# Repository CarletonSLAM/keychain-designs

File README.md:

#PCB Keychains

EAGLE CAD project files for IEEE Carleton University promotional keychains.

(c) Hasith Vidanamadura, 2015

###Todo

- [x] Finish initial layout
- [ ] FInish picking component values for timing control and LEDs.

###License

This is a MIT-licensed project.

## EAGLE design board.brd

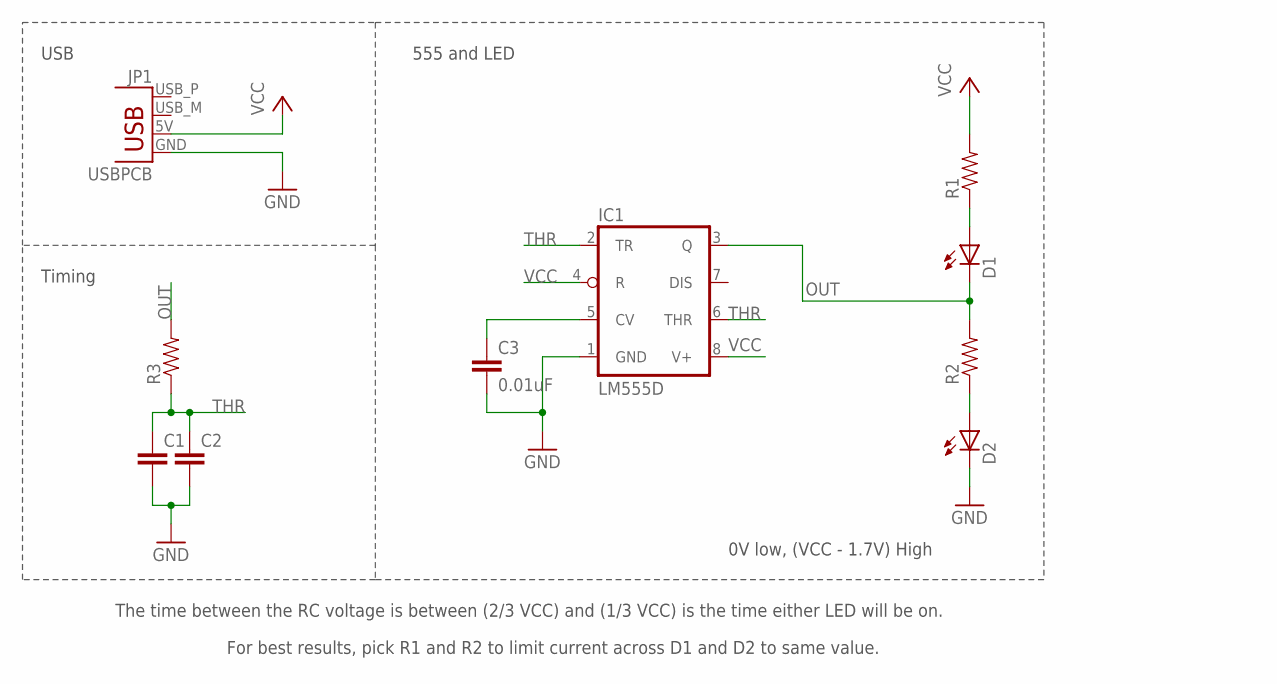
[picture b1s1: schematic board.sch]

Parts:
C1, C2: CAP0805; 0805
C3: 0.01uF; 0805
D1, D2: LEDCHIP-LED0805; CHIP-LED0805
IC1: LM555D; SO08
JP1: USBPCB; USB-A-PCB
R1, R2, R3: RESISTOR0805-RES; 0805

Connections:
GND: C1.2, C2.2, C3.2, D2.C, IC1.1 (GND), JP1.GND
unnamed: D1.A, R1.1
unnamed: C3.1, IC1.5 (CV)
unnamed: D2.A, R2.1
OUT: D1.C, IC1.3 (Q), R2.2, R3.2
THR: C1.1, C2.1, IC1.2 (TR), IC1.6 (THR), R3.1
VCC: IC1.4 (R), IC1.8 (V+), JP1.5V (VBUS), R1.2

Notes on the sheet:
555 and LED
USB
Timing
0V low, (VCC - 1.7V) High
The time between the RC voltage is between (2/3 VCC) and (1/3 VCC) is the time either LED will be on.
For best results, pick R1 and R2 to limit current across D1 and D2 to same value.

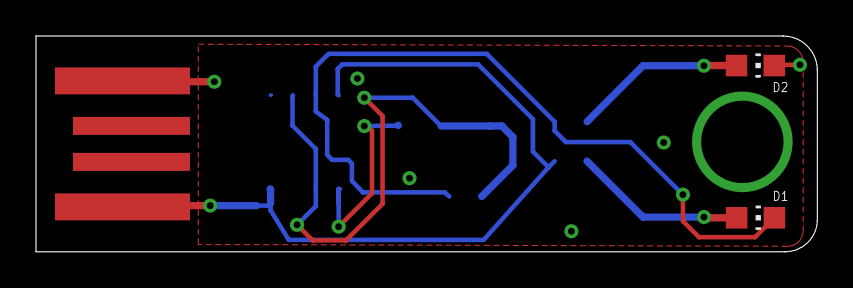
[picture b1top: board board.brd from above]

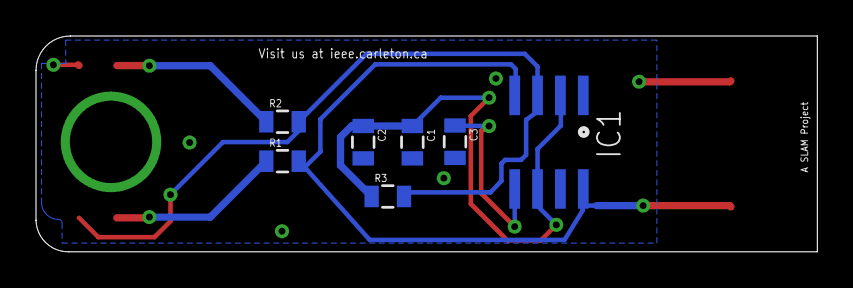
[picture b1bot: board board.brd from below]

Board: 2 copper layers, 43.4 x 12.0 mm, 10 parts (7 on the bottom side), 7 nets.

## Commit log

2015-09-14 Initial commit for PCB keychains

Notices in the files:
parts and their libraries:
SparkFun-Capacitors: Licensing: Creative Commons ShareAlike 4.0 International - https://creativecommons.org/licenses/by-sa/4.0
